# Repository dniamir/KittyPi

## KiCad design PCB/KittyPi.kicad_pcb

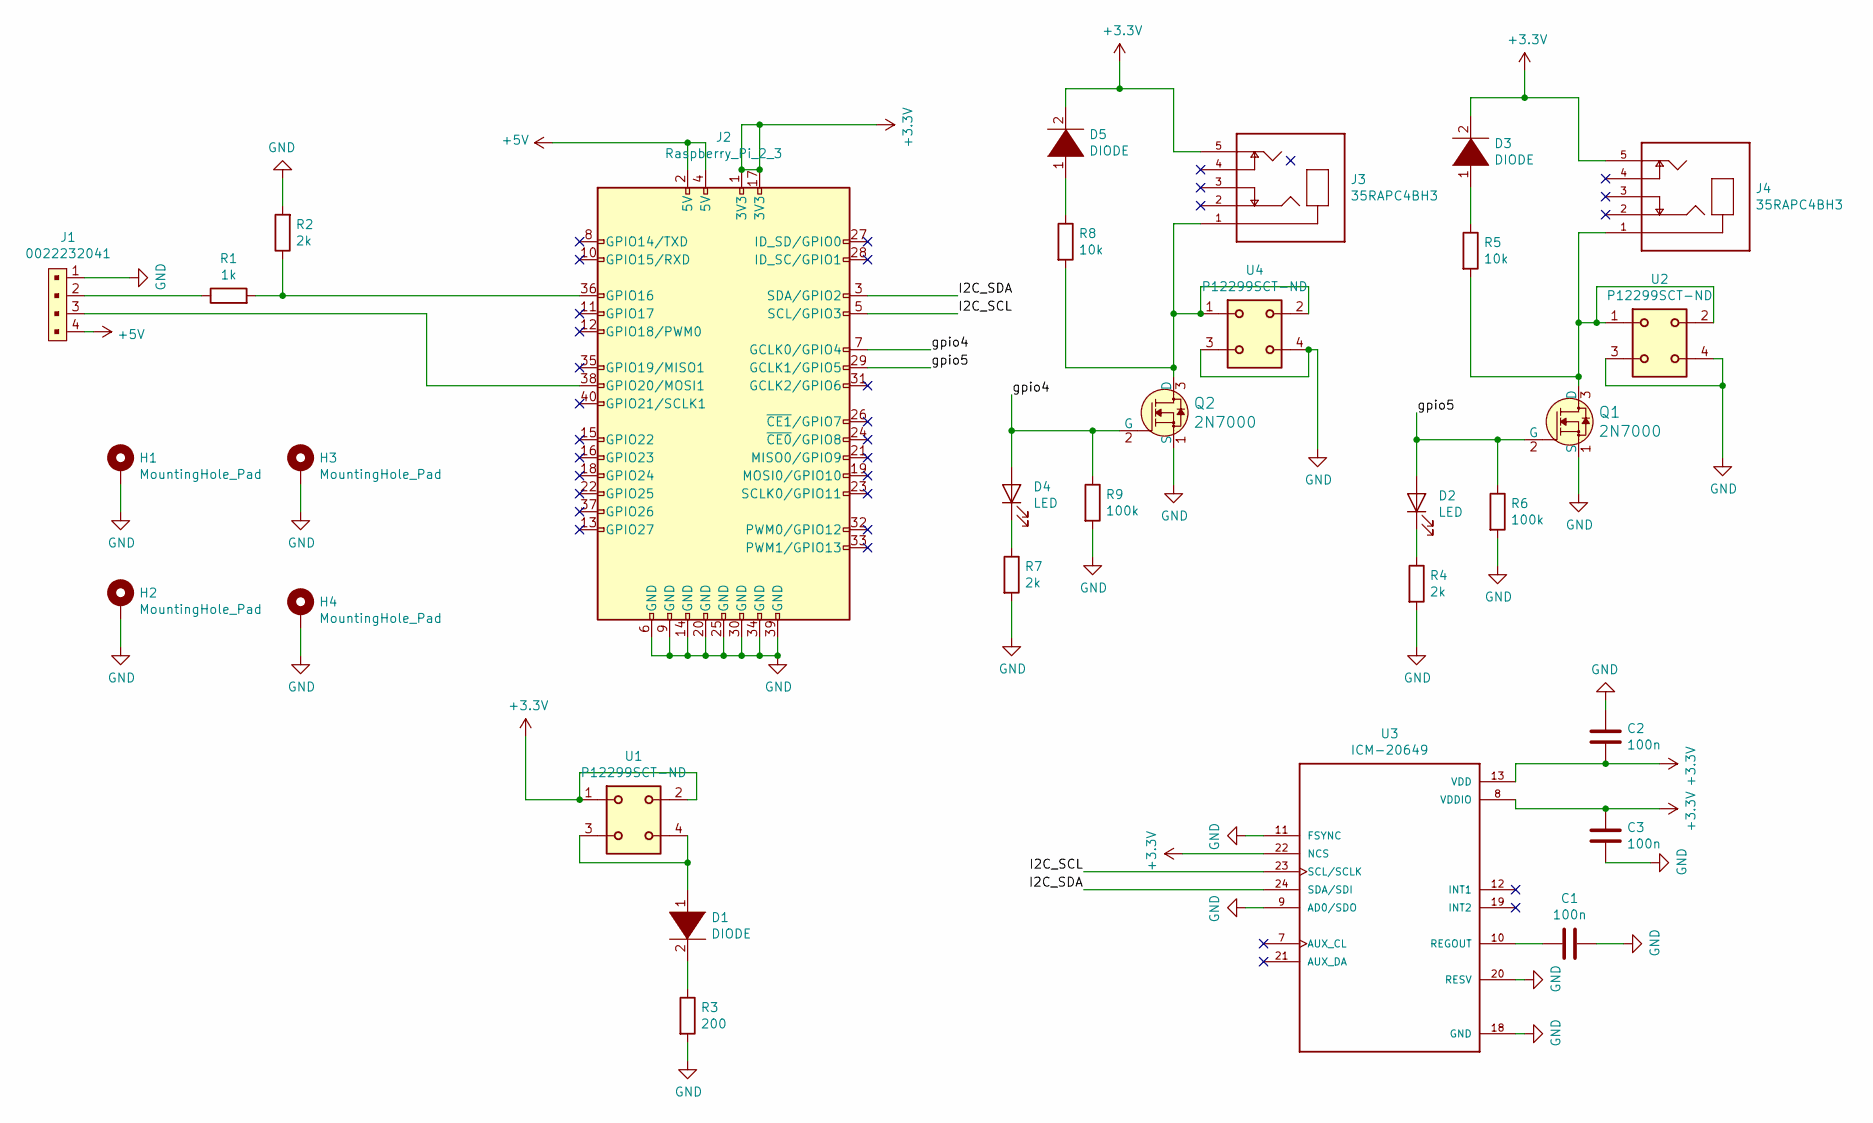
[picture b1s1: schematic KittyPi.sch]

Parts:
C1, C2, C3: 100n; C_0805_2012Metric
D1: DIODE; PinHeader_1x02_P2.54mm_Vertical
D2, D4: LED; LED_D3.0mm
D3, D5: DIODE; R_Axial_DIN0411_L9.9mm_D3.6mm_P15.24mm_Horizontal
H1, H2, H3, H4: MountingHole_Pad; MountingHole_2.5mm_Pad
J1: 0022232041; PinHeader_1x04_P2.54mm_Vertical; MPN 0022232041; Digi-Key_PN WM4202-ND
J2: Raspberry_Pi_2_3; PinHeader_2x20_P2.54mm_Vertical
J3, J4: 35RAPC4BH3
Q1, Q2: 2N7000; TO-92-3; MPN 2N7000; Digi-Key_PN 2N7000FS-ND
R1: 1k; R_0805_2012Metric
R2, R4, R7: 2k; R_0805_2012Metric
R3: 200; R_0805_2012Metric
R5, R8: 10k; R_0805_2012Metric
R6, R9: 100k; R_0805_2012Metric
U1, U2, U4: P12299SCT-ND; Switch_P12943SCT-ND
U3: ICM-20649

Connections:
+3V3: C2.2, C3.1, D3.2 (A), D5.2 (A), J2.1 (3V3), J2.17 (3V3), J3.5, J4.5, U1.1, U1.2, U3.8 (VDDIO), U3.13 (VDD), U3.22 (NCS)
+5V: J1.4, J2.2 (5V), J2.4 (5V)
/I2C_SCL: J2.5 (SCL/GPIO3), U3.23 (SCL/SCLK)
/I2C_SDA: J2.3 (SDA/GPIO2), U3.24 (SDA/SDI)
/gpio4: D4.2 (A), J2.7 (GCLK0/GPIO4), Q2.2 (G), R9.1
/gpio5: D2.2 (A), J2.29 (GCLK1/GPIO5), Q1.2 (G), R6.1
GND: C1.2, C2.1, C3.2, H1.1, H2.1, H3.1, H4.1, J1.1, J2.6 (GND), J2.9 (GND), J2.14 (GND), J2.20 (GND), J2.25 (GND), J2.30 (GND), J2.34 (GND), J2.39 (GND), Q1.1 (S), Q2.1 (S), R2.2, R3.2, R4.2, R6.2, R7.2, R9.2, U2.3, U2.4, U3.9 (AD0/SDO), U3.11 (FSYNC), U3.18 (GND), U3.20 (RESV), U4.3, U4.4
unnamed: C1.1, U3.10 (REGOUT)
unnamed: D1.1 (K), U1.3, U1.4
unnamed: D1.2 (A), R3.1
unnamed: D2.1 (K), R4.1
unnamed: D3.1 (K), R5.1
unnamed: D4.1 (K), R7.1
unnamed: D5.1 (K), R8.1
unnamed: J1.2, R1.1
unnamed: J1.3, J2.38 (GPIO20/MOSI1)
unnamed: J2.36 (GPIO16), R1.2, R2.1
unnamed: J3.1, Q2.3 (D), R8.2, U4.1, U4.2
unnamed: J4.1, Q1.3 (D), R5.2, U2.1, U2.2

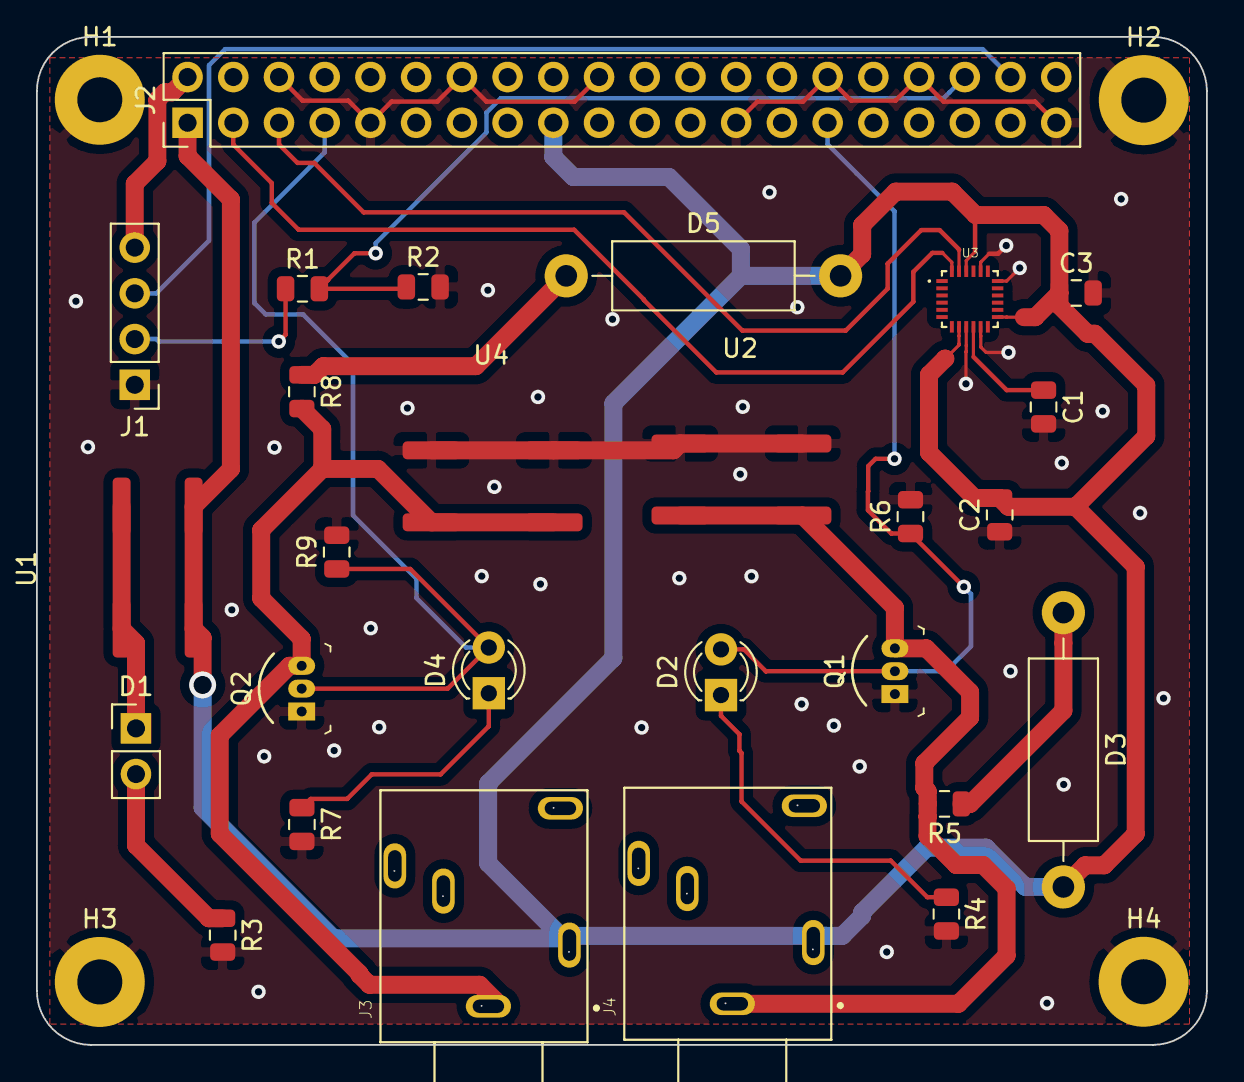
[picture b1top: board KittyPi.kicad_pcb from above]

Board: 2 copper layers, 65.0 x 56.0 mm, 31 parts (0 on the bottom side), 19 nets.

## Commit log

2021-03-14 Initialization of KittyPi repository
2021-11-23 Add functionality for HC SRO4 ultrasonic sensor
2021-11-23 Add STL and PCB files
2021-11-23 Create KittyPi class
2021-11-23 Add sub-repo for chip_systems
